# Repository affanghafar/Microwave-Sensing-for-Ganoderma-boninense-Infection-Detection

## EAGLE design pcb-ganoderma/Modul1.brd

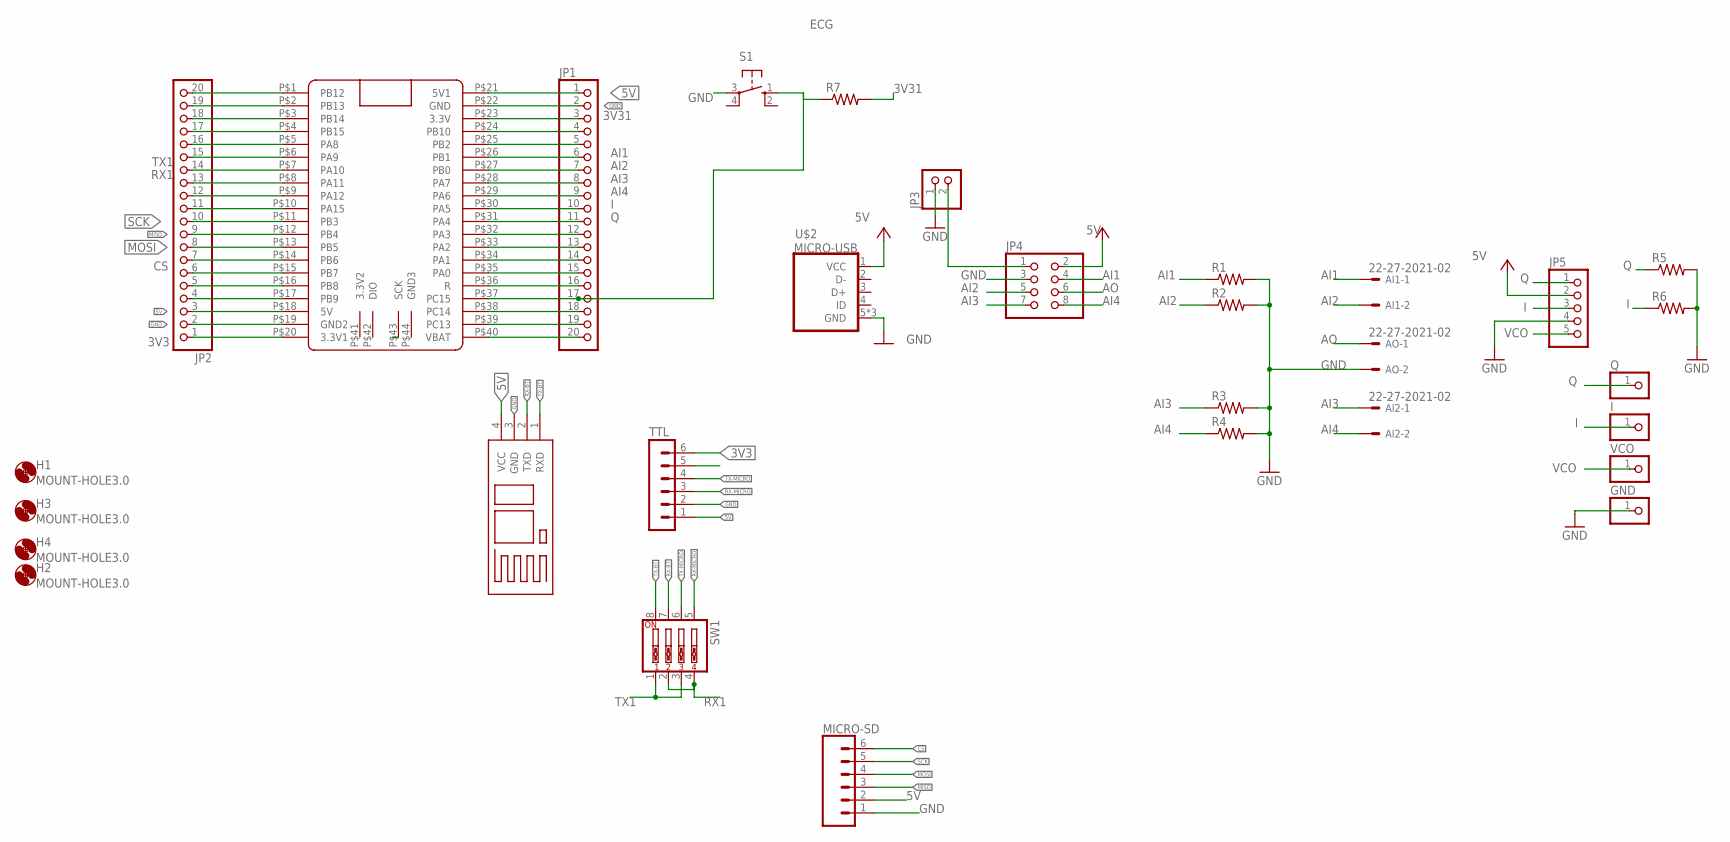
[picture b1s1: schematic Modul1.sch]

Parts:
AI1, AI2: 22-27-2021-02; 6410-02
AO: 22-27-2021-02; 6410-02
B3: BLUETOOTH
GND: PINHD-1X1; 1X01
H1, H2, H3, H4: MOUNT-HOLE3.0; 3,0
I: PINHD-1X1; 1X01
JP1, JP2: PINHD-1X20; 1X20
JP3: PINHD-1X2; 1X02
JP4: PINHD-2X4; 2X04
JP5: PINHD-1X5; 1X05
MICRO-SD: CONN_06SILK_FEMALE_PTH; 1X06@1
Q: PINHD-1X1; 1X01
R1, R2, R3, R4, R5, R6, R7: R-US_0207/12; 0207/12
S1: 10-XX; B3F-10XX
SW1: SW_DIP-4; EDG-04
TTL: MA06-1
U$1: BLACKPILL
U$2: MICRO-USB
VCO: PINHD-1X1; 1X01

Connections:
3V3: JP2.1, TTL.6, U$1.P$20 (3.3V1)
3V31: JP1.3, R7.2, U$1.P$23 (3.3V)
5V: B3.4 (VCC), JP1.1, JP2.3, JP4.2, JP5.2, MICRO-SD.2, TTL.1, U$1.P$18 (5V), U$1.P$21 (5V1), U$2.1 (VCC)
AI1: AI1.1, JP1.6, JP4.4, R1.1, U$1.P$26 (PB1)
AI2: AI1.2, JP1.7, JP4.5, R2.1, U$1.P$27 (PB0)
AI3: AI2.1, JP1.8, JP4.7, R3.1, U$1.P$28 (PA7)
AI4: AI2.2, JP1.9, JP4.8, R4.1, U$1.P$29 (PA6)
AO: AO.1, JP4.6
CS: JP2.7, MICRO-SD.6, U$1.P$14 (PB6)
ECG: JP1.14, U$1.P$34 (PA1)
GND: AO.2, B3.3 (GND), GND.1, JP1.2, JP2.2, JP3.1, JP4.3, JP5.4, MICRO-SD.1, R1.2, R2.2, R3.2, R4.2, R5.2, R6.2, S1.3, TTL.2, U$1.P$19 (GND2), U$1.P$22 (GND), U$2.5 (GND), U$2.GND1 (GND), U$2.GND2 (GND)
I: I.1, JP1.10, JP5.3, R6.1, U$1.P$30 (PA5)
MISO: JP2.9, MICRO-SD.3, U$1.P$12 (PB4)
MOSI: JP2.8, MICRO-SD.4, U$1.P$13 (PB5)
unnamed: JP2.20, U$1.P$1 (PB12)
unnamed: JP2.19, U$1.P$2 (PB13)
unnamed: JP2.18, U$1.P$3 (PB14)
unnamed: JP3.2, JP4.1
unnamed: JP1.17, R7.1, S1.1 (S), U$1.P$37 (PC15)
unnamed: JP1.4, U$1.P$24 (PB10)
unnamed: JP2.11, U$1.P$10 (PA15)
unnamed: JP2.12, U$1.P$9 (PA12)
unnamed: JP2.5, U$1.P$16 (PB8)
unnamed: JP1.20, U$1.P$40 (VBAT)
unnamed: JP1.19, U$1.P$39 (PC13)
unnamed: JP1.18, U$1.P$38 (PC14)
unnamed: JP1.16, U$1.P$36 (R)
unnamed: JP1.5, U$1.P$25 (PB2)
unnamed: JP1.15, U$1.P$35 (PA0)
Q: JP1.11, JP5.1, Q.1, R5.1, U$1.P$31 (PA4)
RX1: JP2.14, SW1.2, SW1.4, U$1.P$7 (PA10)
RX2: JP1.12, U$1.P$32 (PA3)
RX-BT: B3.2 (TXD), SW1.7
RX-MICRO: SW1.5, TTL.3
SCK: JP2.10, MICRO-SD.5, U$1.P$11 (PB3)
SDA: JP2.4, U$1.P$17 (PB9)
SDIO_CK: JP2.17, U$1.P$4 (PB15)
SDIO_D0: JP2.6, U$1.P$15 (PB7)
SDIO_D1: JP2.16, U$1.P$5 (PA8)
SWCK: U$1.P$43 (SCK)
TX1: JP2.15, SW1.1, SW1.3, U$1.P$6 (PA9)
TX2: JP1.13, U$1.P$33 (PA2)
TX6: JP2.13, U$1.P$8 (PA11)
TX-BT: B3.1 (RXD), SW1.8
TX-MICRO: SW1.6, TTL.4
VCO: JP5.5, VCO.1

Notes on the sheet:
ECG

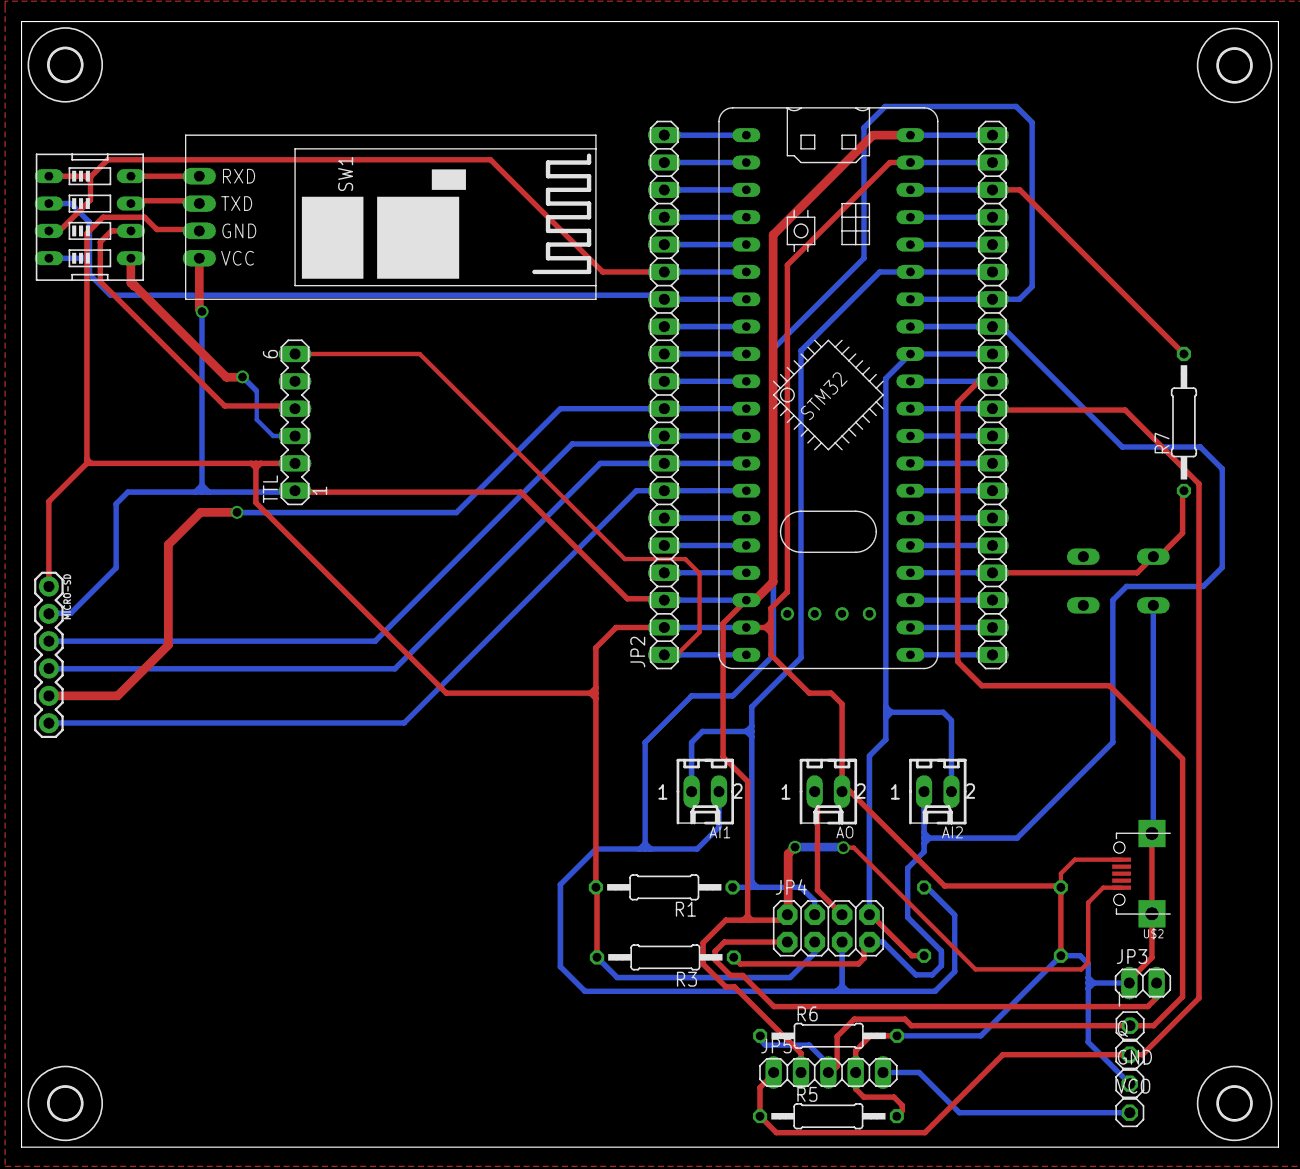
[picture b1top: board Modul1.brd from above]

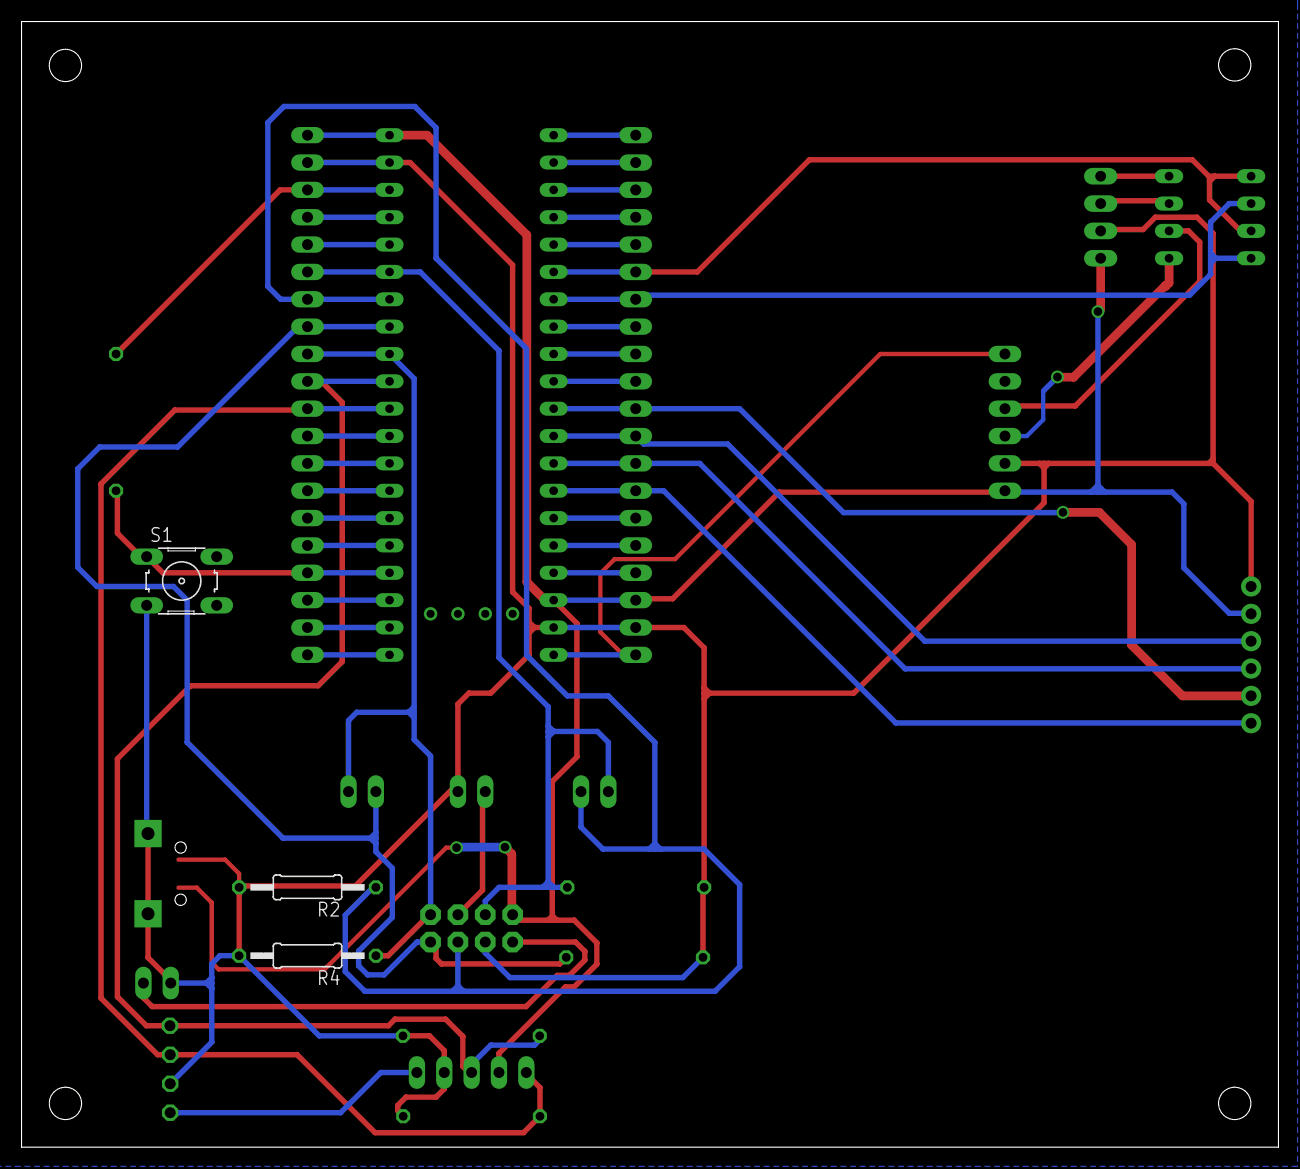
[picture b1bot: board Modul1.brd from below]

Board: 2 copper layers, 116.7 x 104.5 mm, 30 parts (3 on the bottom side), 45 nets.

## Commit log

2026-04-22 Remove README.md file

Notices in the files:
parts and their libraries:
SparkFun-Connectors: Licensing: Creative Commons ShareAlike 4.0 International - https://creativecommons.org/licenses/by-sa/4.0
